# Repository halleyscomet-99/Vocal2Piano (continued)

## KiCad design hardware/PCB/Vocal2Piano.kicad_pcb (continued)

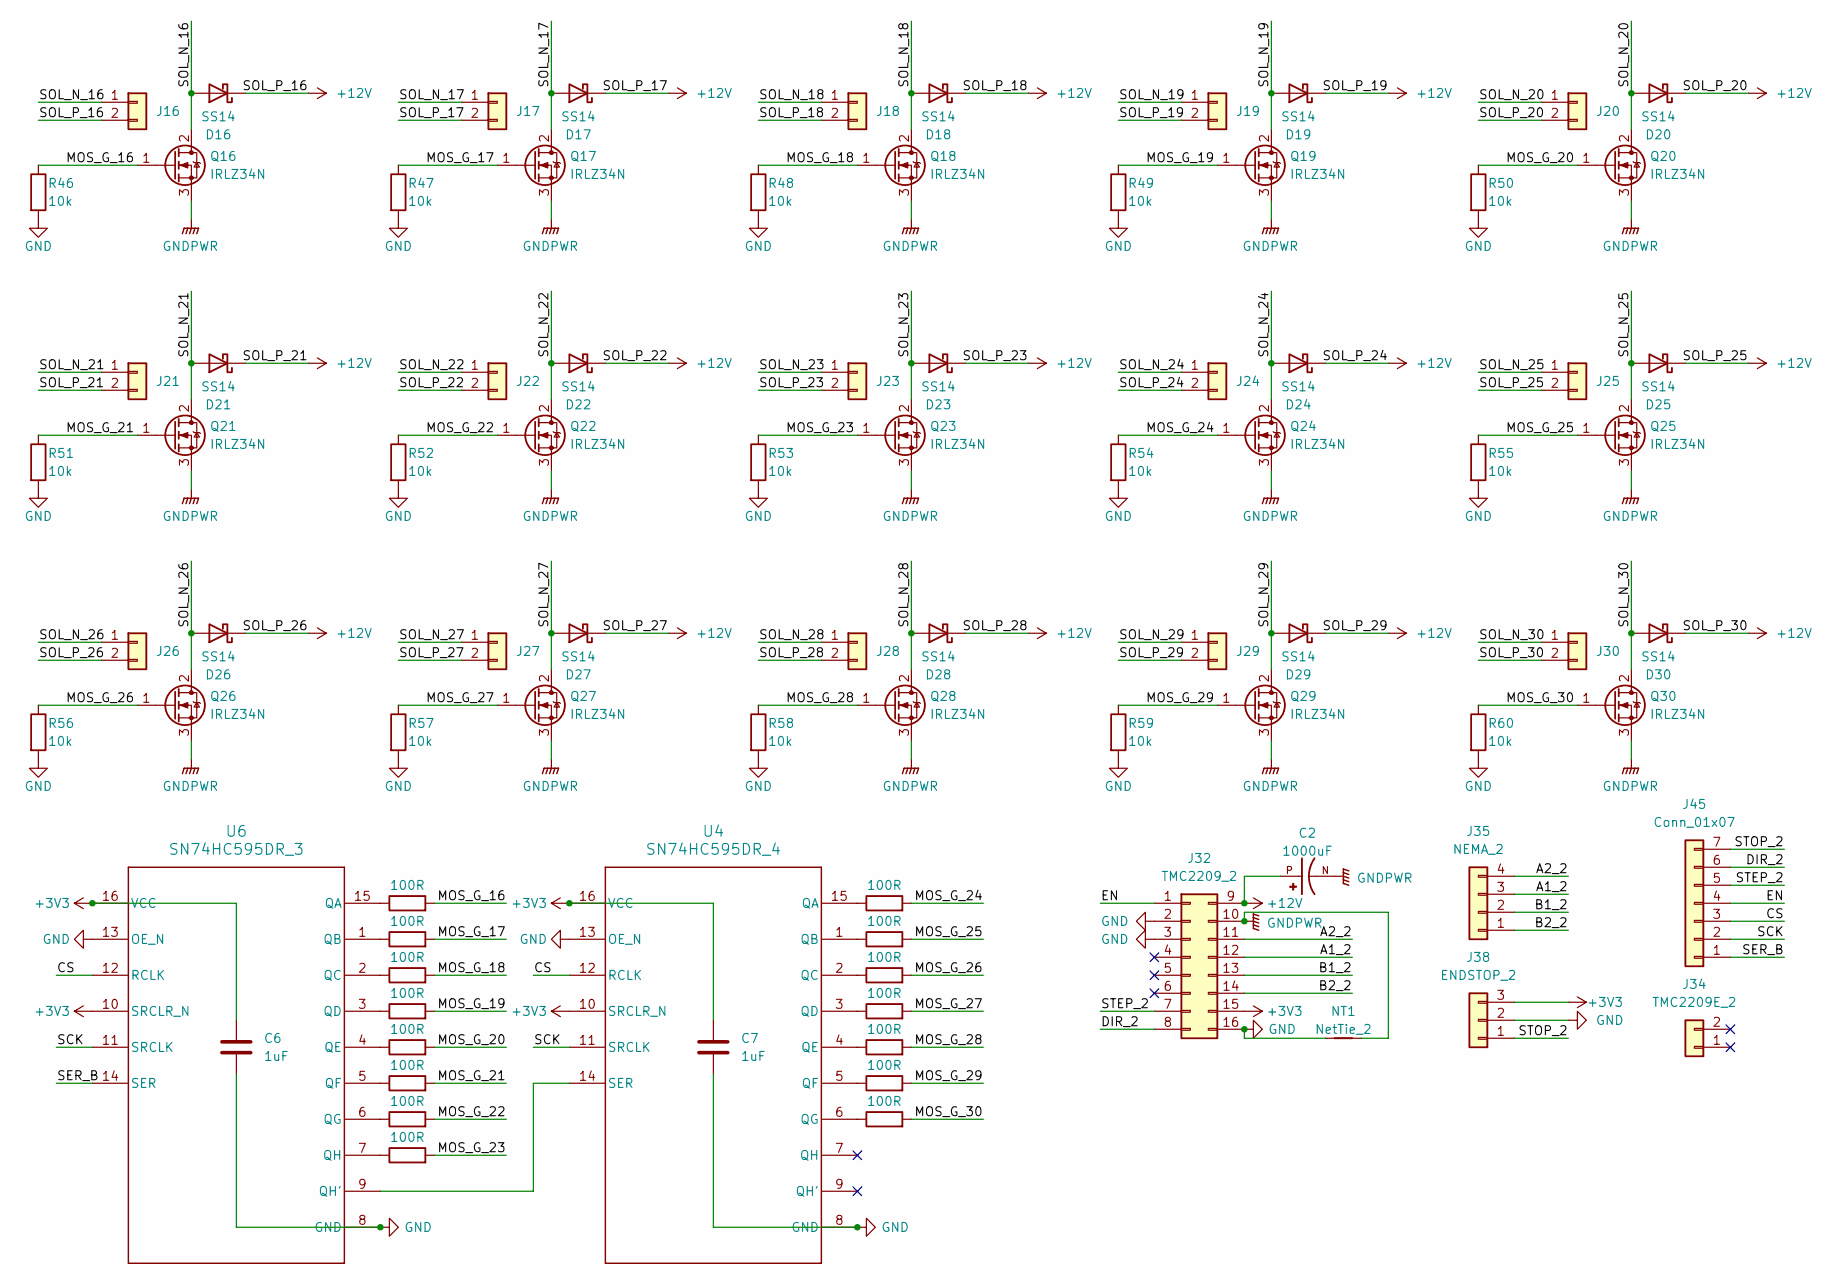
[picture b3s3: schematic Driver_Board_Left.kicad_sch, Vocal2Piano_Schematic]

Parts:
C2: 1000uF; CAPPRD500W60D1250H2000; PARTREV 20-DEC-19
C6, C7: 1uF; C_0805_2012Metric
D16, D17, D18, D19, D20, D21, D22, D23, D24, D25, D26, D27, D28, D29, D30: SS14; D_SMA
J16, J17, J18, J19, J20, J21, J22, J23, J24, J25, J26, J27, J28, J29, J30: Conn_01x02; PinSocket_1x02_P2.54mm_Vertical
J32: TMC2209_2; Pololu_Breakout-16_15.2x20.3mm
J34: TMC2209E_2; PinSocket_1x02_P2.54mm_Vertical
J35: NEMA_2; PinHeader_1x04_P2.54mm_Vertical
J38: ENDSTOP_2; JST_XH_B3B-XH-A_1x03_P2.50mm_Vertical
J45: Conn_01x07; PinSocket_1x07_P2.54mm_Vertical
NT1: NetTie_2; NetTie-2_SMD_Pad0.5mm
Q16, Q17, Q18, Q19, Q20, Q21, Q22, Q23, Q24, Q25, Q26, Q27, Q28, Q29, Q30: IRLZ34N; TO-220-3_Vertical
R17, R18, R19, R20, R21, R22, R23, R24, R25, R26, R27, R28, R29, R30, R31: 100R; R_0805_2012Metric
R46, R47, R48, R49, R50, R51, R52, R53, R54, R55, R56, R57, R58, R59, R60: 10k; R_0805_2012Metric
U4: SN74HC595DR_4; D0016A_N
U6: SN74HC595DR_3; D0016A_N

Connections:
+3V3: C6.1, C7.1, J32.15 (VDD), J38.3, U4.10 (SRCLR_N), U4.16 (VCC), U6.10 (SRCLR_N), U6.16 (VCC); also elsewhere on the board
+12V: C2.P, D16.1 (K), D17.1 (K), D18.1 (K), D19.1 (K), D20.1 (K), D21.1 (K), D22.1 (K), D23.1 (K), D24.1 (K), D25.1 (K), D26.1 (K), D27.1 (K), D28.1 (K), D29.1 (K), D30.1 (K), J16.2, J17.2, J18.2, J19.2, J20.2, J21.2, J22.2, J23.2, J24.2, J25.2, J26.2, J27.2, J28.2, J29.2, J30.2, J32.9 (VM); also elsewhere on the board
/Driver_Board_Left/A1_2: J32.12 (A1), J35.3
/Driver_Board_Left/A2_2: J32.11 (A2), J35.4
/Driver_Board_Left/B1_2: J32.13 (B1), J35.2
/Driver_Board_Left/B2_2: J32.14 (B2), J35.1
/Driver_Board_Left/CS: J45.3, U4.12 (RCLK), U6.12 (RCLK)
/Driver_Board_Left/DIR_2: J32.8 (DIR), J45.6
/Driver_Board_Left/EN: J32.1 (EN), J45.4
/Driver_Board_Left/MOS_G_16: Q16.1 (G), R17.2, R46.1
/Driver_Board_Left/MOS_G_17: Q17.1 (G), R18.2, R47.1
/Driver_Board_Left/MOS_G_18: Q18.1 (G), R19.2, R48.1
/Driver_Board_Left/MOS_G_19: Q19.1 (G), R20.2, R49.1
/Driver_Board_Left/MOS_G_20: Q20.1 (G), R21.2, R50.1
/Driver_Board_Left/MOS_G_21: Q21.1 (G), R22.2, R51.1
/Driver_Board_Left/MOS_G_22: Q22.1 (G), R23.2, R52.1
/Driver_Board_Left/MOS_G_23: Q23.1 (G), R24.2, R53.1
/Driver_Board_Left/MOS_G_24: Q24.1 (G), R25.2, R54.1
/Driver_Board_Left/MOS_G_25: Q25.1 (G), R26.2, R55.1
/Driver_Board_Left/MOS_G_26: Q26.1 (G), R27.2, R56.1
/Driver_Board_Left/MOS_G_27: Q27.1 (G), R28.2, R57.1
/Driver_Board_Left/MOS_G_28: Q28.1 (G), R29.2, R58.1
/Driver_Board_Left/MOS_G_29: Q29.1 (G), R30.2, R59.1
/Driver_Board_Left/MOS_G_30: Q30.1 (G), R31.2, R60.1
/Driver_Board_Left/SCK: J45.2, U4.11 (SRCLK), U6.11 (SRCLK)
/Driver_Board_Left/SER_B: J45.1, U6.14 (SER)
/Driver_Board_Left/SOL_N_16: D16.2 (A), J16.1, Q16.2 (D)
/Driver_Board_Left/SOL_N_17: D17.2 (A), J17.1, Q17.2 (D)
/Driver_Board_Left/SOL_N_18: D18.2 (A), J18.1, Q18.2 (D)
/Driver_Board_Left/SOL_N_19: D19.2 (A), J19.1, Q19.2 (D)
/Driver_Board_Left/SOL_N_20: D20.2 (A), J20.1, Q20.2 (D)
/Driver_Board_Left/SOL_N_21: D21.2 (A), J21.1, Q21.2 (D)
/Driver_Board_Left/SOL_N_22: D22.2 (A), J22.1, Q22.2 (D)
/Driver_Board_Left/SOL_N_23: D23.2 (A), J23.1, Q23.2 (D)
/Driver_Board_Left/SOL_N_24: D24.2 (A), J24.1, Q24.2 (D)
/Driver_Board_Left/SOL_N_25: D25.2 (A), J25.1, Q25.2 (D)
/Driver_Board_Left/SOL_N_26: D26.2 (A), J26.1, Q26.2 (D)
/Driver_Board_Left/SOL_N_27: D27.2 (A), J27.1, Q27.2 (D)
/Driver_Board_Left/SOL_N_28: D28.2 (A), J28.1, Q28.2 (D)
/Driver_Board_Left/SOL_N_29: D29.2 (A), J29.1, Q29.2 (D)
/Driver_Board_Left/SOL_N_30: D30.2 (A), J30.1, Q30.2 (D)
/Driver_Board_Left/STEP_2: J32.7 (STEP), J45.5
/Driver_Board_Left/STOP_2: J38.1, J45.7
GND: C6.2, C7.2, J32.2 (MS1), J32.3 (MS2), J32.16 (GND), J38.2, NT1.1, R46.2, R47.2, R48.2, R49.2, R50.2, R51.2, R52.2, R53.2, R54.2, R55.2, R56.2, R57.2, R58.2, R59.2, R60.2, U4.8 (GND), U4.13 (OE_N), U6.8 (GND), U6.13 (OE_N); also elsewhere on the board
GNDPWR: C2.N, J32.10 (GND), NT1.2, Q16.3 (S), Q17.3 (S), Q18.3 (S), Q19.3 (S), Q20.3 (S), Q21.3 (S), Q22.3 (S), Q23.3 (S), Q24.3 (S), Q25.3 (S), Q26.3 (S), Q27.3 (S), Q28.3 (S), Q29.3 (S), Q30.3 (S); also elsewhere on the board
unnamed: R25.1, U4.15 (QA)
unnamed: R26.1, U4.1 (QB)
unnamed: R27.1, U4.2 (QC)
unnamed: R28.1, U4.3 (QD)
unnamed: R29.1, U4.4 (QE)
unnamed: R30.1, U4.5 (QF)
unnamed: R31.1, U4.6 (QG)
unnamed: U4.14 (SER), U6.9 (QH')
unnamed: R17.1, U6.15 (QA)
unnamed: R18.1, U6.1 (QB)
unnamed: R19.1, U6.2 (QC)
unnamed: R20.1, U6.3 (QD)
unnamed: R21.1, U6.4 (QE)
unnamed: R22.1, U6.5 (QF)
unnamed: R23.1, U6.6 (QG)
unnamed: R24.1, U6.7 (QH)

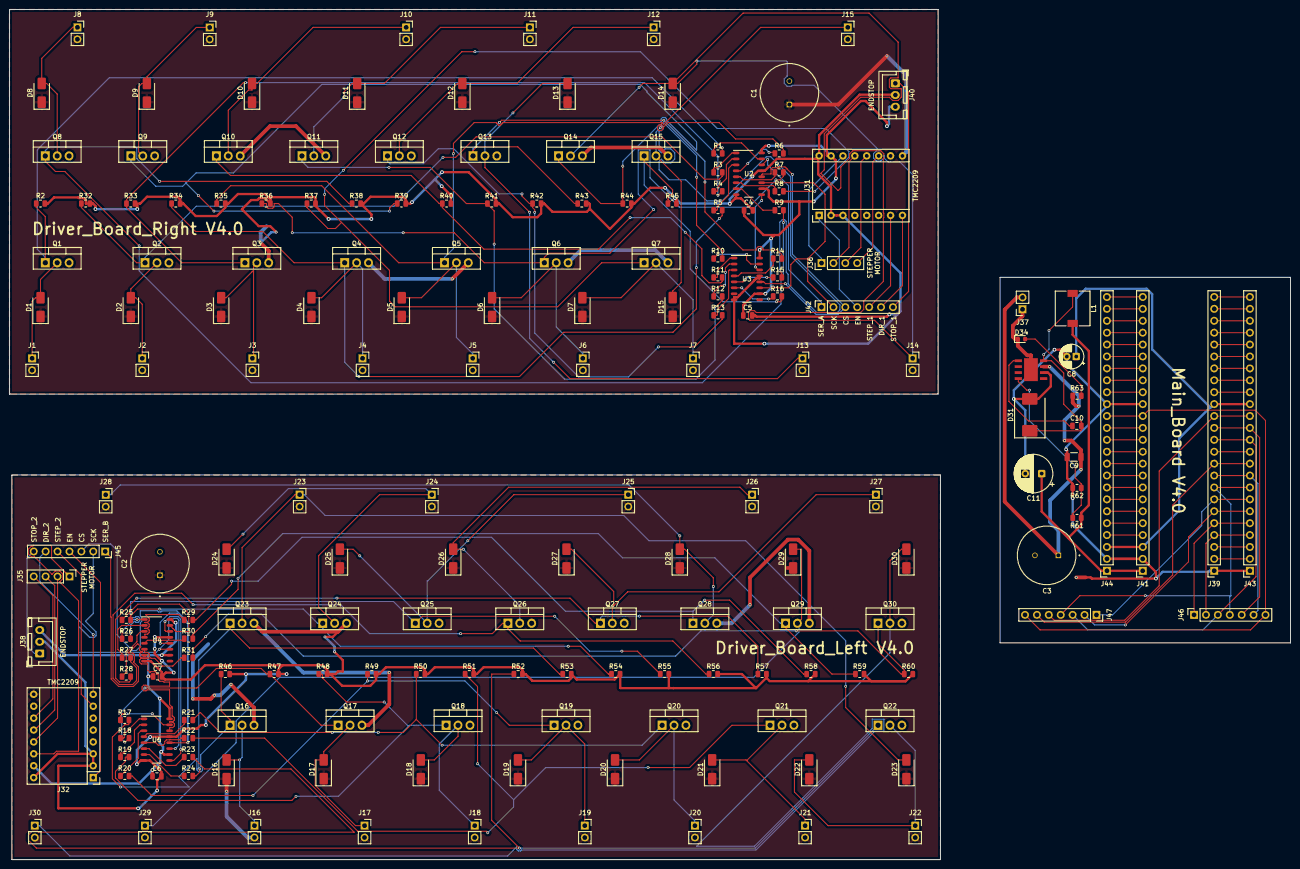
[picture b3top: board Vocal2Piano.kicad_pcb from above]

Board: 2 copper layers, 273.3 x 181.4 mm, 190 parts (0 on the bottom side), 165 nets.

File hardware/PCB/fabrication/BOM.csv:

Designator,Comment,Footprint
L1,15uH,L_7.3x7.3_H4.5
"J17,J30,J4,J25,J22,J16,J26,J21,J29,J20,J10,J5,J24,J18,J14,J3,J8,J11,J1,J6,J23,J12,J19,J9,J15,J2,J7,J28,J13,J27",Conn_01x02,PinSocket_1x02_P2.54mm_Vertical
"R19,R14,R23,R21,R25,R9,R26,R11,R4,R28,R31,R7,R24,R5,R17,R6,R29,R1,R8,R3,R12,R22,R20,R27,R18,R13,R15,R10,R16,R30",100R,R_0805_2012Metric
"C4,C5,C7,C6",1uF,C_0805_2012Metric
"C1,C3,C2",1000uF,CAPPRD500W60D1250H2000
C11,470uF,CP_Radial_D8.0mm_P3.50mm
D31,B340,D_SMC
"D14,D24,D21,D20,D13,D12,D19,D5,D17,D26,D6,D23,D16,D1,D3,D9,D30,D29,D18,D11,D28,D27,D4,D10,D8,D7,D15,D25,D2,D22",SS14,D_SMA
J39,TEENSY_L,PinSocket_1x24_P2.54mm_Vertical
"Q13,Q21,Q26,Q18,Q29,Q23,Q19,Q20,Q30,Q17,Q25,Q4,Q22,Q6,Q8,Q9,Q11,Q14,Q5,Q2,Q7,Q1,Q10,Q27,Q12,Q24,Q28,Q16,Q3,Q15",IRLZ34N,TO-220-3_Vertical
C9,22uF,C_1206_3216Metric
"R45,R58,R50,R35,R38,R44,R61,R53,R40,R41,R55,R52,R42,R48,R43,R46,R2,R49,R51,R32,R34,R47,R59,R54,R57,R60,R56,R36,R37,R33,R39",10k,R_0805_2012Metric
J31,TMC2209_1,Pololu_Breakout-16_15.2x20.3mm
J41,TEENSY_R,PinSocket_1x24_P2.54mm_Vertical
J36,NEMA_1,PinHeader_1x04_P2.54mm_Vertical
J44,TEENSY_BREAKOUT_R,PinSocket_1x24_P2.54mm_Vertical
"J42,J45",Conn_01x07,PinSocket_1x07_P2.54mm_Vertical
U6,SN74HC595DR_3,D0016A_N
U5,TPS5430DDAR,DDA0008J_NV
J37,PWR,PinSocket_1x02_P2.54mm_Vertical
R63,4.7k,R_0805_2012Metric
U3,SN74HC595DR_2,D0016A_N
C8,10uF,CP_Radial_D5.0mm_P2.00mm
U2,SN74HC595DR_1,D0016A_N
R62,3.24k,R_0805_2012Metric
J43,TEENSY_BREAKOUT_L,PinSocket_1x24_P2.54mm_Vertical
J38,ENDSTOP_2,JST_XH_B3B-XH-A_1x03_P2.50mm_Vertical
J46,DRIVER_RIGHT,PinSocket_1x07_P2.54mm_Vertical
D34,POWER LED,LED_0603_1608Metric
U4,SN74HC595DR_4,D0016A_N
J47,DRIVER_LEFT,PinSocket_1x07_P2.54mm_Vertical
J40,ENDSTOP_1,JST_XH_B3B-XH-A_1x03_P2.50mm_Vertical
C10,10nF,C_0805_2012Metric
J35,NEMA_2,PinHeader_1x04_P2.54mm_Vertical
J32,TMC2209_2,Pololu_Breakout-16_15.2x20.3mm

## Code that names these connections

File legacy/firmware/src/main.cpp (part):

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 *
 * PIN ASSIGNMENTS
 * ---------------
 *  Pin 2   STEP_1     Right stepper pulse
 *  Pin 3   DIR_1      Right stepper direction
 *  Pin 4   STEP_2     Left stepper pulse
 *  Pin 5   DIR_2      Left stepper direction
 *  Pin 6   EN         Shared stepper enable (active LOW)
 *  Pin 7   STOP_1     Right endstop (INPUT_PULLUP, LOW = triggered)
 *  Pin 8   STOP_2     Left endstop
 *  Pin 10  CS         Shared 74HC595 latch (rising edge latches both boards)
 *  Pin 11  SER_A      Right board shift register data
 *  Pin 12  SER_B      Left board shift register data
 *  Pin 13  SCK        Shared shift register clock
 *
 * SHIFT REGISTER TOPOLOGY
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constexpr uint8_t PIN_STOP_R = 7;   // INPUT_PULLUP, LOW = triggered
constexpr uint8_t PIN_STOP_L = 8;
constexpr uint8_t PIN_CS     = 10;  // 74HC595 latch (shared)
constexpr uint8_t PIN_SER_A  = 11;  // right board data
constexpr uint8_t PIN_SER_B  = 12;  // left board data
constexpr uint8_t PIN_SCK    = 13;  // clock (shared)


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    // Shift 16 bits, MSB first
    for (int i = 15; i >= 0; i--) {
        digitalWrite(PIN_SCK,   LOW);
        digitalWrite(PIN_SER_A, (maskR >> i) & 1u);
        digitalWrite(PIN_SER_B, (maskL >> i) & 1u);
        delayMicroseconds(1);
        digitalWrite(PIN_SCK,   HIGH);
        delayMicroseconds(1);
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    // Shift register output pins
    pinMode(PIN_CS,    OUTPUT);  digitalWrite(PIN_CS,    LOW);
    pinMode(PIN_SCK,   OUTPUT);  digitalWrite(PIN_SCK,   LOW);
    pinMode(PIN_SER_A, OUTPUT);  digitalWrite(PIN_SER_A, LOW);
    pinMode(PIN_SER_B, OUTPUT);  digitalWrite(PIN_SER_B, LOW);

    // Clear all solenoids on startup
    releaseAll();
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
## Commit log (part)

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2026-03-03 Hardware/PCB: Completed and finalized the PCB layout for fabrication.
2026-03-03 Updated .gitignore for KiCad 9.0 and macOS development to ensure only core design files and libraries are tracked, while keeping the repository free of temporary backups, logs, and system junk.
2026-03-03 Cleaned .DS_Store files in the GitHub repo.
2026-03-11 Updated README.md for now.
2026-03-23 Completed Layer 2 pipeline, firmware, and project documentation
    Layer 2 (Python, host):
    - add MIDI2Chords.py: Krumhansl key detection, Markov chord sequencer,
    melody-affinity voicing, corpus training via --train flag
    - add MIDI2Piano.py: rail planner, Teensy serial driver, sim fallback
    Firmware (Teensy 4.1, PlatformIO):
    - add firmware/src/main.cpp: solenoid control via 74HC595 shift registers,
2026-03-23 Updated README.md format
2026-04-06 Flake8ed all files and deployed the front-end website.
2026-04-06 Fix: lowercase filenames
2026-04-06 Fix: Pinned deps for Python 3.11; Added nixpacks.toml
2026-04-06 Fix: Strip heavy deps for Railway 4GB limit, voice-only server.
2026-04-06 Railway deployment, capability detection, and Flake8 cleanup
    Backend:
    - add Railway deployment config (Procfile, requirements.txt, nixpacks.toml)
    - update health endpoint to return capabilities/server_mode/limits
    auto-detects full vs lite mode based on installed dependencies
    Frontend:
    - FileMode v8: fetch /health on mount, grey out unavailable source
2026-04-06 Deployed to Vercel + Railway; added capability detection and lite-mode UI.
2026-04-10 Updated website to visualize solenoids' movements.
